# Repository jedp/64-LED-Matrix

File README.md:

# 64 LED Matrix breakout board

64 x 0604 LEDs.

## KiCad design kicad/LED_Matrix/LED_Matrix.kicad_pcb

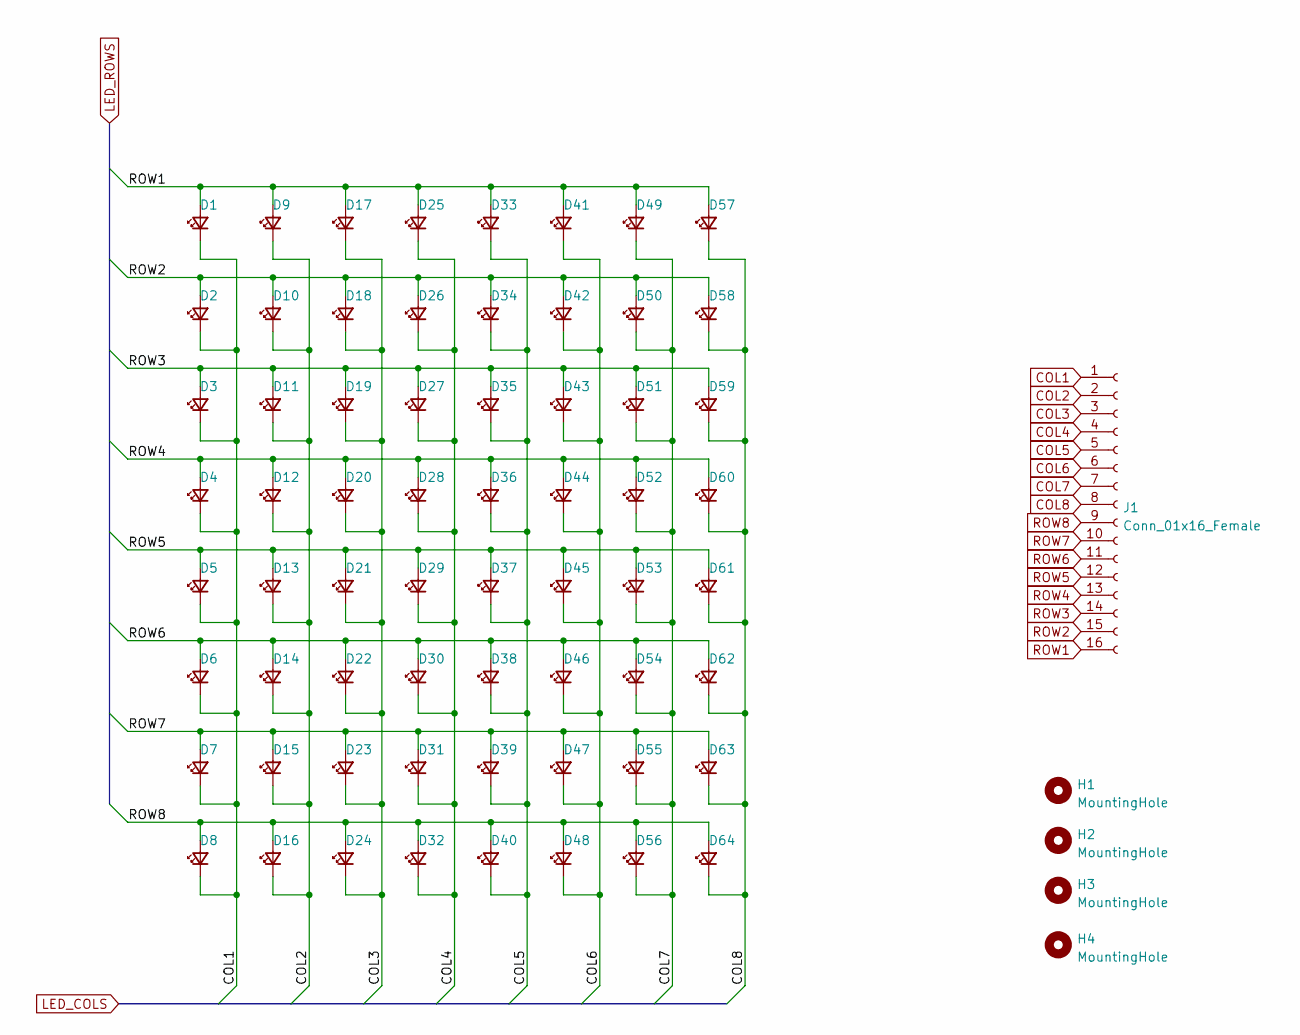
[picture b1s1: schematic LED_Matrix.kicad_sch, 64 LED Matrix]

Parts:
D1, D2, D3, D4, D5, D6, D7, D8, D9, D10, D11, D12, D13, D14, D15, D16, D17, D18, D19, D20, D21, D22, D23, D24, D25, D26, D27, D28, D29, D30, D31, D32, D33, D34, D35, D36, D37, D38, D39, D40, D41, D42, D43, D44, D45, D46, D47, D48, D49, D50, D51, D52, D53, D54, D55, D56, D57, D58, D59, D60, D61, D62, D63, D64: LED_Small; LED_0603_1608Metric
H1, H2, H3, H4: MountingHole; MountingHole_3.2mm_M3
J1: Conn_01x16_Female; PinHeader_1x16_P2.54mm_Vertical

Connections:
COL1: D1.1 (K), D2.1 (K), D3.1 (K), D4.1 (K), D5.1 (K), D6.1 (K), D7.1 (K), D8.1 (K), J1.1
COL2: D9.1 (K), D10.1 (K), D11.1 (K), D12.1 (K), D13.1 (K), D14.1 (K), D15.1 (K), D16.1 (K), J1.2
COL3: D17.1 (K), D18.1 (K), D19.1 (K), D20.1 (K), D21.1 (K), D22.1 (K), D23.1 (K), D24.1 (K), J1.3
COL4: D25.1 (K), D26.1 (K), D27.1 (K), D28.1 (K), D29.1 (K), D30.1 (K), D31.1 (K), D32.1 (K), J1.4
COL5: D33.1 (K), D34.1 (K), D35.1 (K), D36.1 (K), D37.1 (K), D38.1 (K), D39.1 (K), D40.1 (K), J1.5
COL6: D41.1 (K), D42.1 (K), D43.1 (K), D44.1 (K), D45.1 (K), D46.1 (K), D47.1 (K), D48.1 (K), J1.6
COL7: D49.1 (K), D50.1 (K), D51.1 (K), D52.1 (K), D53.1 (K), D54.1 (K), D55.1 (K), D56.1 (K), J1.7
COL8: D57.1 (K), D58.1 (K), D59.1 (K), D60.1 (K), D61.1 (K), D62.1 (K), D63.1 (K), D64.1 (K), J1.8
ROW1: D1.2 (A), D9.2 (A), D17.2 (A), D25.2 (A), D33.2 (A), D41.2 (A), D49.2 (A), D57.2 (A), J1.16
ROW2: D2.2 (A), D10.2 (A), D18.2 (A), D26.2 (A), D34.2 (A), D42.2 (A), D50.2 (A), D58.2 (A), J1.15
ROW3: D3.2 (A), D11.2 (A), D19.2 (A), D27.2 (A), D35.2 (A), D43.2 (A), D51.2 (A), D59.2 (A), J1.14
ROW4: D4.2 (A), D12.2 (A), D20.2 (A), D28.2 (A), D36.2 (A), D44.2 (A), D52.2 (A), D60.2 (A), J1.13
ROW5: D5.2 (A), D13.2 (A), D21.2 (A), D29.2 (A), D37.2 (A), D45.2 (A), D53.2 (A), D61.2 (A), J1.12
ROW6: D6.2 (A), D14.2 (A), D22.2 (A), D30.2 (A), D38.2 (A), D46.2 (A), D54.2 (A), D62.2 (A), J1.11
ROW7: D7.2 (A), D15.2 (A), D23.2 (A), D31.2 (A), D39.2 (A), D47.2 (A), D55.2 (A), D63.2 (A), J1.10
ROW8: D8.2 (A), D16.2 (A), D24.2 (A), D32.2 (A), D40.2 (A), D48.2 (A), D56.2 (A), D64.2 (A), J1.9

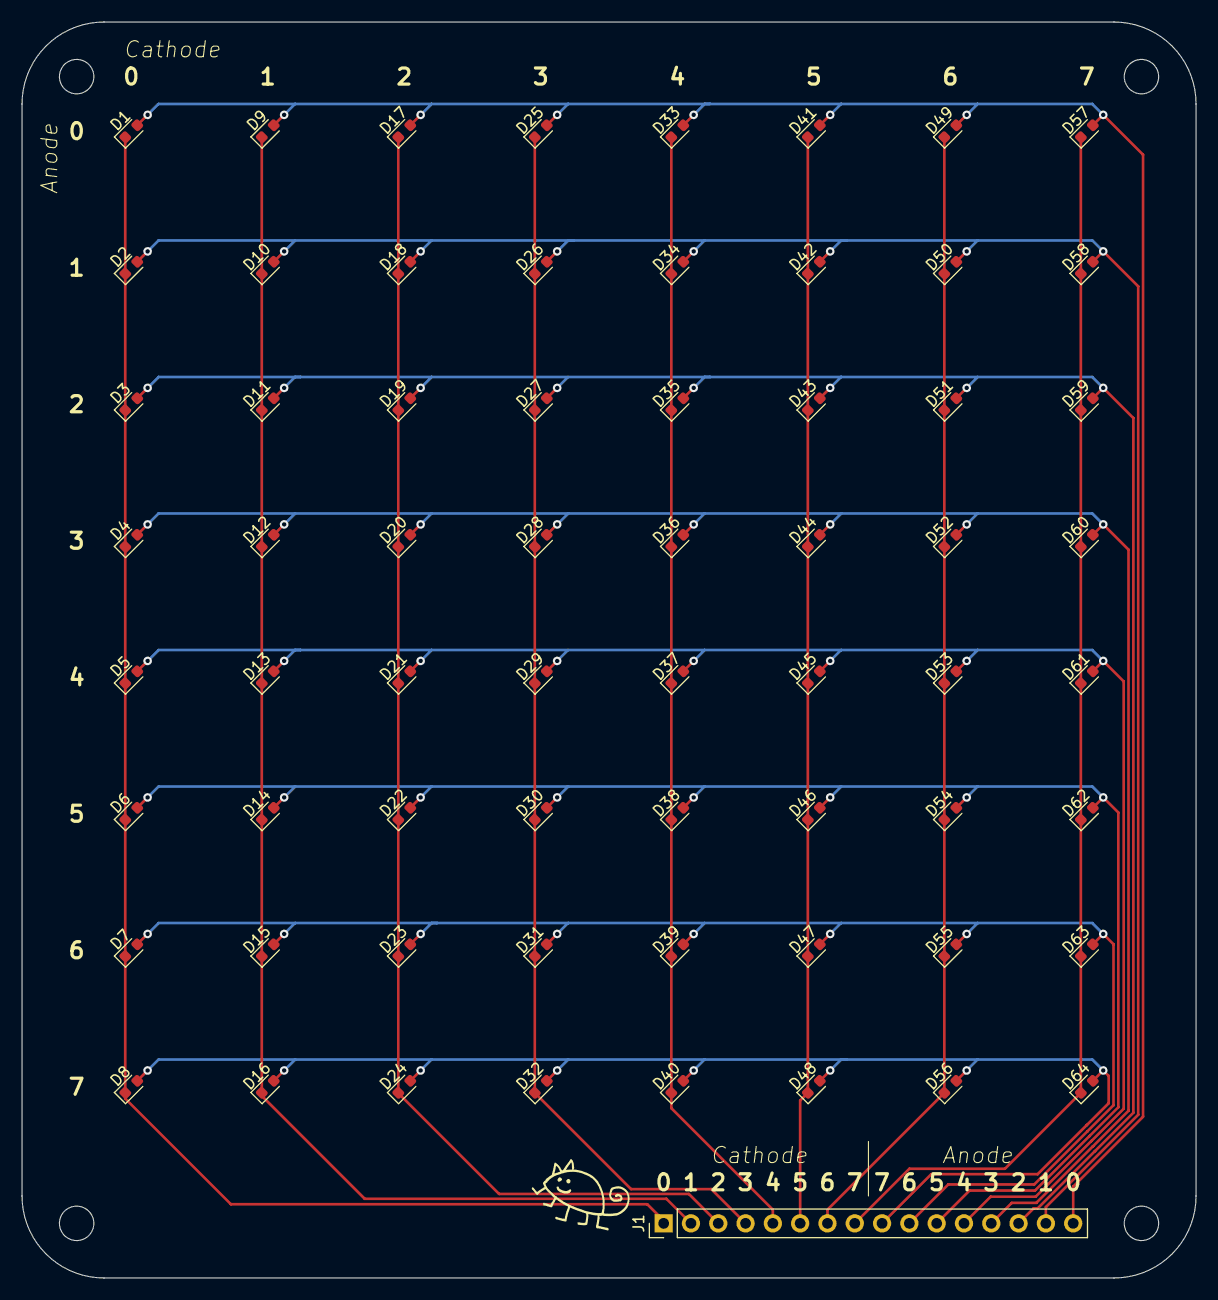
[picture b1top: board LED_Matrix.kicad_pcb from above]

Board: 2 copper layers, 109.2 x 116.8 mm, 69 parts (0 on the bottom side), 16 nets.

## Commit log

2022-12-31 64 LED matrix
